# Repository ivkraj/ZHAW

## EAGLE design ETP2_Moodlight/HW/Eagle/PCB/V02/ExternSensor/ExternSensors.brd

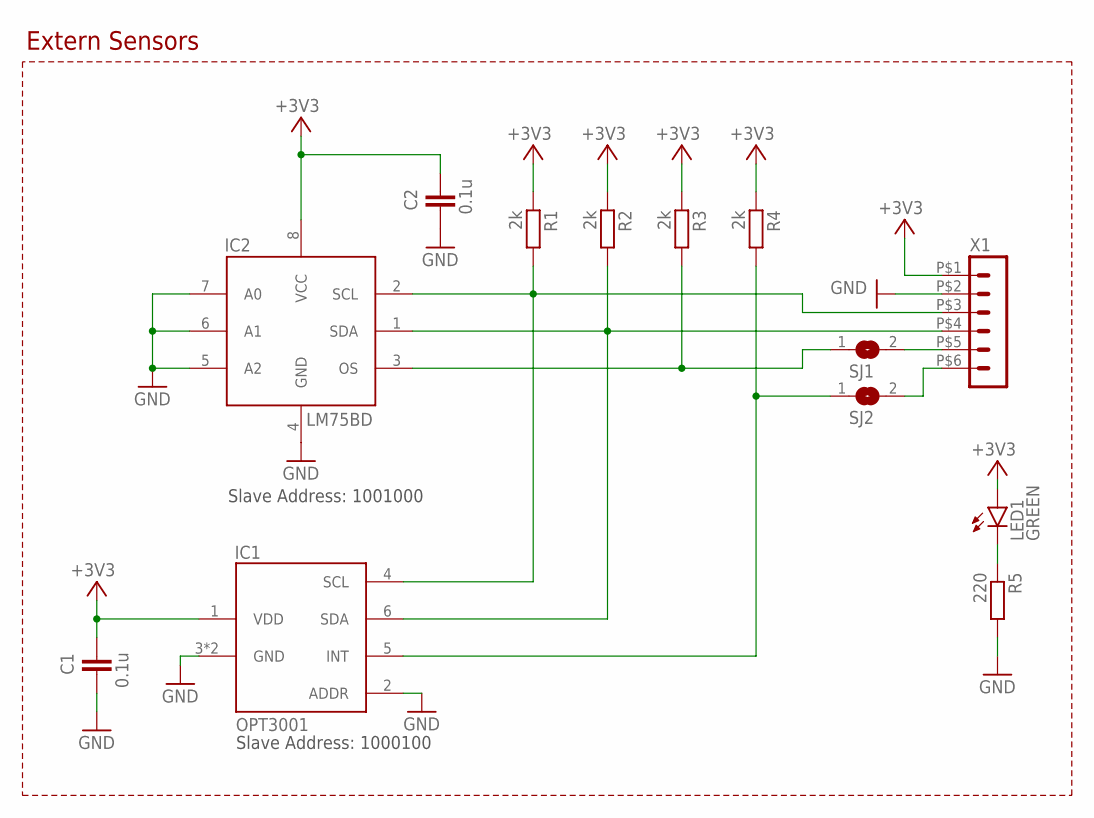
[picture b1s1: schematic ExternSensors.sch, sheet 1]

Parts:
C1, C2: 0.1u; C0805K
IC1: OPT3001
IC2: LM75BD; SO8_LM75
LED1: GREEN; CHIP-LED0805
R1, R2, R3, R4: 2k; R0805
R5: 220; R0805
SJ1, SJ2: SJ
X1: HEADER_POS6_43650-0612; 43650-0612

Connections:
+3V3: C1.2, C2.2, IC1.1 (VDD), IC2.8 (VCC), LED1.A, R1.1, R2.1, R3.1, R4.1, X1.P$1 (1)
GND: C1.1, C2.1, IC1.2 (ADDR), IC1.3 (GND), IC1.P$1 (GND), IC2.4 (GND), IC2.5 (A2), IC2.6 (A1), IC2.7 (A0), R5.2, X1.P$2 (2)
unnamed: LED1.C, R5.1
unnamed: SJ2.2, X1.P$6 (6)
unnamed: IC2.3 (OS), R3.2, SJ1.1
unnamed: IC1.5 (INT), R4.2, SJ2.1
unnamed: SJ1.2, X1.P$5 (5)
SCL: IC1.4 (SCL), IC2.2 (SCL), R1.2, X1.P$3 (3)
SDA: IC1.6 (SDA), IC2.1 (SDA), R2.2, X1.P$4 (4)

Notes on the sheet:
Extern Sensors
Slave Address: 1000100
Slave Address: 1001000

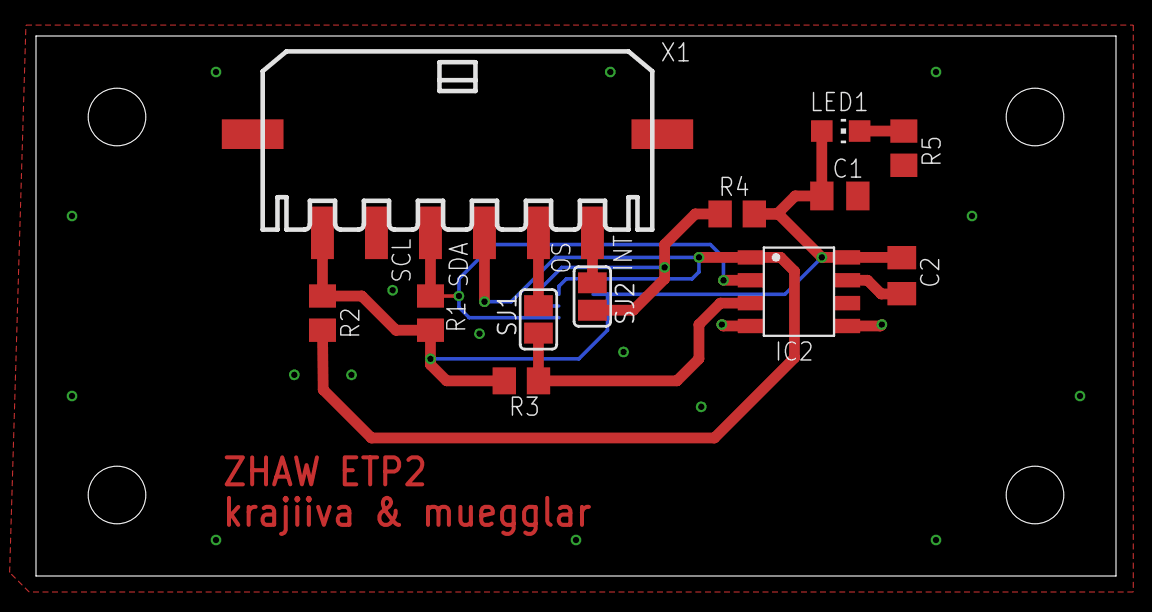
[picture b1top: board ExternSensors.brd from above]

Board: 2 copper layers, 60.0 x 30.0 mm, 13 parts (1 on the bottom side), 9 nets.

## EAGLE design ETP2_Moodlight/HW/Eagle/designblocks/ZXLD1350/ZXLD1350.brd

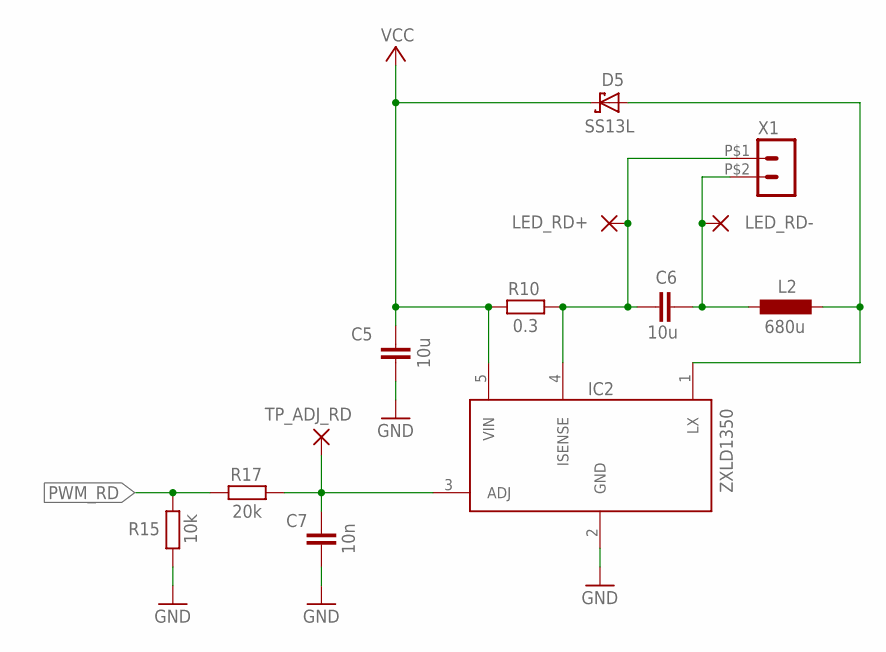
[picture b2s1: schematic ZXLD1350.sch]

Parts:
C5, C6: 10u; C0805K
C7: 10n; C0805K
D5: SS13L; SUB-SMA
IC2: ZXLD1350; TSOT23-5L
L2: 680u; POWER-CHOKE_WE-PD
LED_RD+: TESTPOINT; 3,2/1,6
LED_RD-: TESTPOINT; 3,2/1,6
R10: 0.3; R1206
R15: 10k; R0805
R17: 20k; R0805
TP_ADJ_RD: TESTPOINT; 3,2/1,6
X1: HEADER_POS2_43650-0215; 43650-0215

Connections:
GND: C5.2, C7.2, IC2.2 (GND), R15.1
LED_R+: C6.1, IC2.4 (ISENSE), LED_RD+.1, R10.2, X1.P$1 (1)
LED_R-: C6.2, L2.1, LED_RD-.1, X1.P$2 (2)
unnamed: D5.A, IC2.1 (LX), L2.2
unnamed: C7.1, IC2.3 (ADJ), R17.1, TP_ADJ_RD.1
PWM_RD: R15.2, R17.2
VCC: C5.1, D5.C, IC2.5 (VIN), R10.1

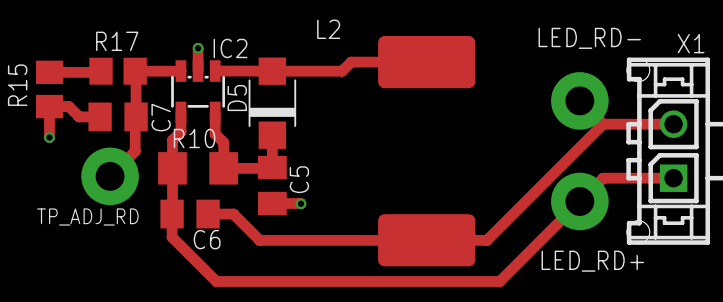
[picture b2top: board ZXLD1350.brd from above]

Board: 2 copper layers, 13 parts (0 on the bottom side), 7 nets.

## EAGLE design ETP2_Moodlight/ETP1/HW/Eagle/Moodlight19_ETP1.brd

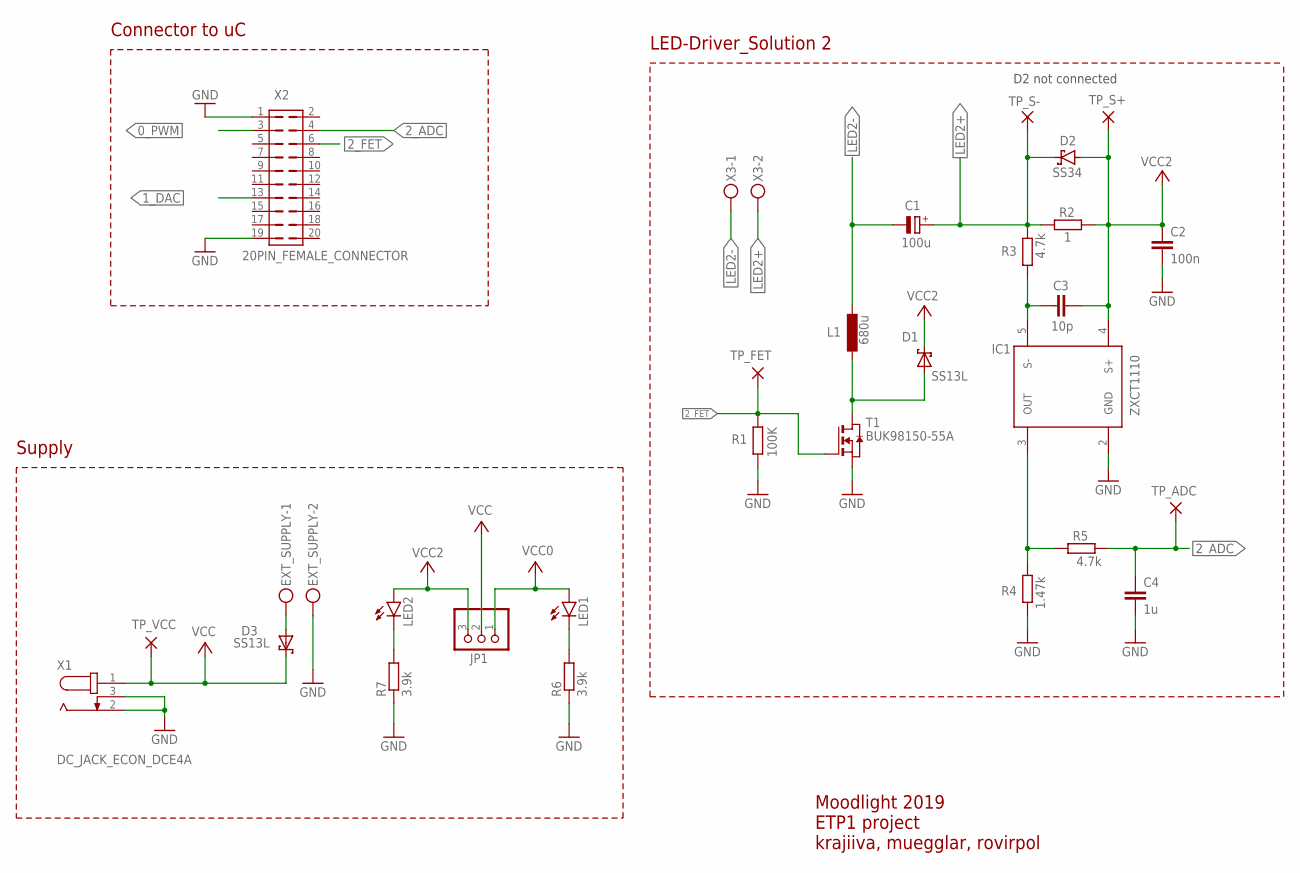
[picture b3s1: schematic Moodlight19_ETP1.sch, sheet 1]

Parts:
C1: 100u; E3,5-8
C2: 100n; C0805K
C3: 10p; C0805K
C4: 1u; C0805K
D1, D3: SS13L; SUB-SMA
D2: SS34; SMC
EXT_SUPPLY: MKDSN1,5/2-5,08
IC1: ZXCT1110; SOT23-5
JP1: PINHD-1X3; 1X03
L1: 680u; POWER-CHOKE_WE-PD
LED1, LED2: LED3MM
R1: 100K; R0805
R2: 1; R1206
R3, R5: 4.7k; R0805
R4: 1.47k; R0805
R6, R7: 3.9k; R0805
T1: BUK98150-55A; SOT223
TP_ADC: WIREPAD4,16O1,6; 4,16O1,6
TP_FET: WIREPAD4,16O1,6; 4,16O1,6
TP_S+: WIREPAD4,16O1,6; 4,16O1,6
TP_S-: WIREPAD4,16O1,6; 4,16O1,6
TP_VCC: WIREPAD4,16O1,6; 4,16O1,6
X1: DC_JACK_ECON_DCE4A
X2: 20PIN_FEMALE_CONNECTOR
X3: MKDSN1,5/2-5,08

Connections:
0_PWM: X2.3; also elsewhere on the board
1_DAC: X2.13; also elsewhere on the board
2_ADC: C4.1, R5.1, TP_ADC.1, X2.4
2_FET: R1.2, T1.1 (G), TP_FET.1, X2.6
A: D3.A, EXT_SUPPLY.1
GND: C2.2, C4.2, EXT_SUPPLY.2, IC1.2 (GND), R1.1, R4.1, R6.1, R7.1, T1.3 (S), X1.2, X1.3, X2.1, X2.19; also elsewhere on the board
LED2+: C1.+, D2.C, R2.1, R3.2, TP_S-.1, X3.2
LED2-: C1.-, L1.1, X3.1
unnamed: LED1.K (C), R6.2
unnamed: LED2.K (C), R7.2
unnamed: IC1.3 (OUT), R4.2, R5.2
unnamed: C3.1, IC1.5 (S-), R3.1
unnamed: D1.A, L1.2, T1.2 (D), T1.4 (D)
VCC: D3.C, JP1.2, TP_VCC.1, X1.1
VCC0: JP1.1, LED1.A; also elsewhere on the board
VCC2: C2.1, C3.2, D1.C, D2.A, IC1.4 (S+), JP1.3, LED2.A, R2.2, TP_S+.1

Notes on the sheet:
Connector to uC
Supply
LED-Driver_Solution 2
Moodlight 2019 ETP1 project krajiiva, muegglar, rovirpol
D2 not connected

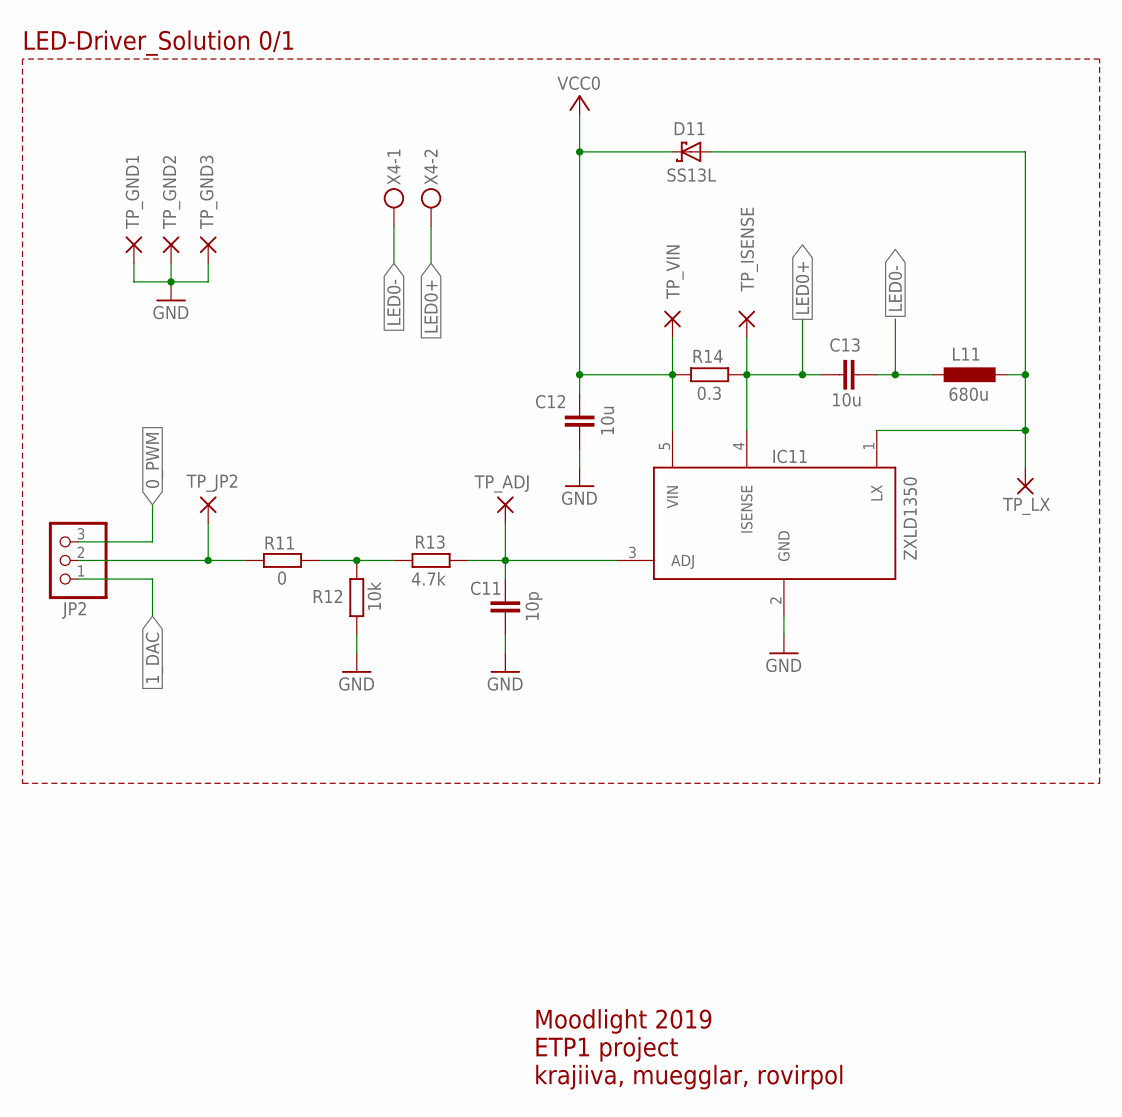
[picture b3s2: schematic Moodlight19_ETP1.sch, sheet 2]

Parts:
C11: 10p; C0805K
C12, C13: 10u; C0805K
D11: SS13L; SUB-SMA
IC11: ZXLD1350; TSOT23-5L
JP2: PINHD-1X3; 1X03
L11: 680u; POWER-CHOKE_WE-PD
R11: 0; R0805
R12: 10k; R0805
R13: 4.7k; R0805
R14: 0.3; R1206
TP_ADJ: WIREPAD4,16O1,6; 4,16O1,6
TP_GND1, TP_GND2, TP_GND3: WIREPAD4,16O1,6; 4,16O1,6
TP_ISENSE: WIREPAD4,16O1,6; 4,16O1,6
TP_JP2: WIREPAD4,16O1,6; 4,16O1,6
TP_LX: WIREPAD4,16O1,6; 4,16O1,6
TP_VIN: WIREPAD4,16O1,6; 4,16O1,6
X4: MKDSN1,5/2-5,08

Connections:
0_ADJUST: JP2.2, R11.1, TP_JP2.1
0_PWM: JP2.3; also elsewhere on the board
1_DAC: JP2.1; also elsewhere on the board
GND: C11.2, C12.2, IC11.2 (GND), R12.1, TP_GND1.1, TP_GND2.1, TP_GND3.1; also elsewhere on the board
LED0+: C13.1, IC11.4 (ISENSE), R14.2, TP_ISENSE.1, X4.2
LED0-: C13.2, L11.1, X4.1
unnamed: R11.2, R12.2, R13.2
unnamed: D11.A, IC11.1 (LX), L11.2, TP_LX.1
unnamed: C11.1, IC11.3 (ADJ), R13.1, TP_ADJ.1
VCC0: C12.1, D11.C, IC11.5 (VIN), R14.1, TP_VIN.1; also elsewhere on the board

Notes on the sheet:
LED-Driver_Solution 0/1
Moodlight 2019 ETP1 project krajiiva, muegglar, rovirpol

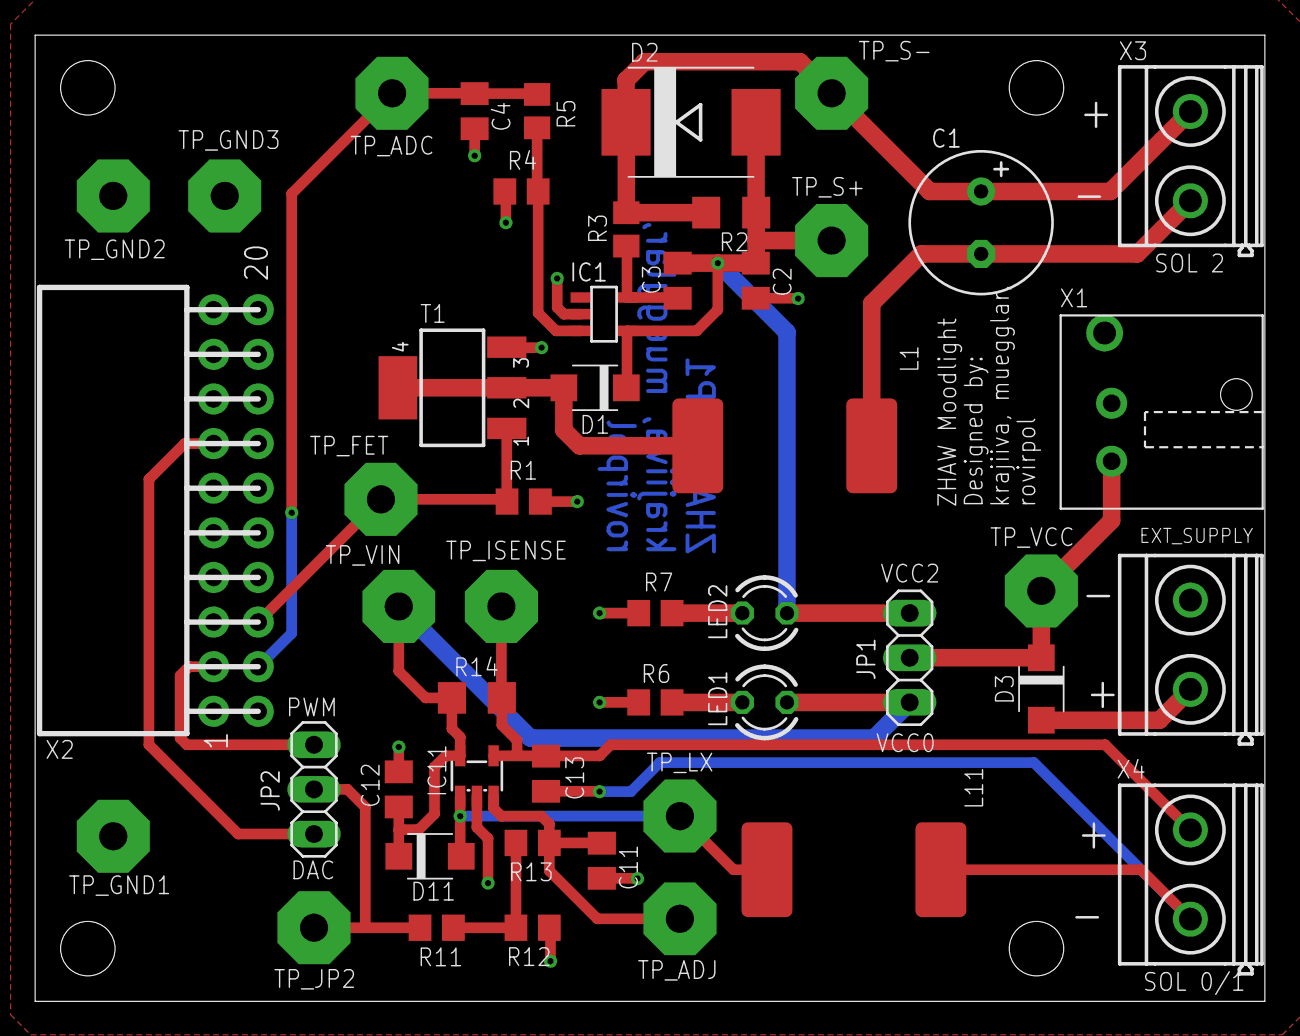
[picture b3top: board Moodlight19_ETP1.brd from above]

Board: 2 copper layers, 70.0 x 55.0 mm, 49 parts (0 on the bottom side), 22 nets.

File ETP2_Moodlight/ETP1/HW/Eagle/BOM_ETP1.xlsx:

Part | Value | Device | Package | Description
C1 | 100u | CPOL-EUE3.5-8 | E3,5-8 | POLARIZED CAPACITOR, European symbol
C2 | 100n | C-EUC0805K | C0805K | CAPACITOR, European symbol
C3 | 10p | C-EUC0805K | C0805K | CAPACITOR, European symbol
C4 | 1u | C-EUC0805K | C0805K | CAPACITOR, European symbol
C11 | 10p | C-EUC0805K | C0805K | CAPACITOR, European symbol
C12 | 10u | C-EUC0805K | C0805K | CAPACITOR, European symbol
C13 | 10u | C-EUC0805K | C0805K | CAPACITOR, European symbol
D1 | SS13L | SS13L | SUB-SMA | Schottky-Diode
D2 | SS34 | SCHOTTKY-DIODESMC | SMC | Schottky Diode
D3 | SS13L | SS13L | SUB-SMA | Schottky-Diode
D11 | SS13L | SS13L | SUB-SMA | Schottky-Diode
EXT_SUPPLY | MKDSN1,5/2-5,08 | MKDSN1,5/2-5,08 | MKDSN1,5/2-5,08 | MKDSN 1,5/ 2-5,08 Printklemme
IC1 | ZXCT1110 | ZXCT1110 | SOT23-5 | ZXCT1110
IC11 | ZXLD1350 | ZXLD1350 | TSOT23-5L | ZXLD1350
JP1 |  | PINHD-1X3 | 1X03 | PIN HEADER
JP2 |  | PINHD-1X3 | 1X03 | PIN HEADER
L1 | 680u | POWER-CHOKE_WE-PD | POWER-CHOKE_WE-PD | POWER-CHOKE_WE-PD
L11 | 680u | POWER-CHOKE_WE-PD | POWER-CHOKE_WE-PD | POWER-CHOKE_WE-PD
LED1 |  | LED3MM | LED3MM | LED
LED2 |  | LED3MM | LED3MM | LED
R1 | 100K | R-EU_R0805 | R0805 | RESISTOR, European symbol
R2 | 1 | R-EU_R1206 | R1206 | RESISTOR, European symbol
R3 | 4.7k | R-EU_R0805 | R0805 | RESISTOR, European symbol
R4 | 1.47k | R-EU_R0805 | R0805 | RESISTOR, European symbol
R5 | 4.7k | R-EU_R0805 | R0805 | RESISTOR, European symbol
R6 | 1.2k | R-EU_R0805 | R0805 | RESISTOR, European symbol
R7 | 1.2k | R-EU_R0805 | R0805 | RESISTOR, European symbol
R11 | 2k | R-EU_R0805 | R0805 | RESISTOR, European symbol
R12 | 1.3k | R-EU_R0805 | R0805 | RESISTOR, European symbol
R13 | 4.7k | R-EU_R0805 | R0805 | RESISTOR, European symbol
R14 | 0.3 | R-EU_R1206 | R1206 | RESISTOR, European symbol
T1 | BUK98150-55A | BUK98150-55A | SOT223 | n-Kanal-MOS-FET
TP_ADC | WIREPAD4,16O1,6 | WIREPAD4,16O1,6 | 4,16O1,6 | Wire PAD connect wire on PCB
TP_ADJ | WIREPAD4,16O1,6 | WIREPAD4,16O1,6 | 4,16O1,6 | Wire PAD connect wire on PCB
TP_FET | WIREPAD4,16O1,6 | WIREPAD4,16O1,6 | 4,16O1,6 | Wire PAD connect wire on PCB
TP_GND1 | WIREPAD4,16O1,6 | WIREPAD4,16O1,6 | 4,16O1,6 | Wire PAD connect wire on PCB
TP_GND2 | WIREPAD4,16O1,6 | WIREPAD4,16O1,6 | 4,16O1,6 | Wire PAD connect wire on PCB
TP_GND3 | WIREPAD4,16O1,6 | WIREPAD4,16O1,6 | 4,16O1,6 | Wire PAD connect wire on PCB
TP_ISENSE | WIREPAD4,16O1,6 | WIREPAD4,16O1,6 | 4,16O1,6 | Wire PAD connect wire on PCB
TP_JP2 | WIREPAD4,16O1,6 | WIREPAD4,16O1,6 | 4,16O1,6 | Wire PAD connect wire on PCB
TP_LX | WIREPAD4,16O1,6 | WIREPAD4,16O1,6 | 4,16O1,6 | Wire PAD connect wire on PCB
TP_S+ | WIREPAD4,16O1,6 | WIREPAD4,16O1,6 | 4,16O1,6 | Wire PAD connect wire on PCB
TP_S- | WIREPAD4,16O1,6 | WIREPAD4,16O1,6 | 4,16O1,6 | Wire PAD connect wire on PCB
TP_VCC | WIREPAD4,16O1,6 | WIREPAD4,16O1,6 | 4,16O1,6 | Wire PAD connect wire on PCB
TP_VIN | WIREPAD4,16O1,6 | WIREPAD4,16O1,6 | 4,16O1,6 | Wire PAD connect wire on PCB
X1 | DC_JACK_ECON_DCE4A | DC_JACK_ECON_DCE4A | DC_JACK_ECON_DCE4A | DC_JACK_ECON_DCE4A
X2 | 20PIN_FEMALE_CONNECTOR | 20PIN_FEMALE_CONNECTOR | 20PIN_FEMALE_CONNECTOR | Buchsenleiste 20Pol 90Â°
X3 | MKDSN1,5/2-5,08 | MKDSN1,5/2-5,08 | MKDSN1,5/2-5,08 | MKDSN 1,5/ 2-5,08 Printklemme
X4 | MKDSN1,5/2-5,08 | MKDSN1,5/2-5,08 | MKDSN1,5/2-5,08 | MKDSN 1,5/ 2-5,08 Printklemme

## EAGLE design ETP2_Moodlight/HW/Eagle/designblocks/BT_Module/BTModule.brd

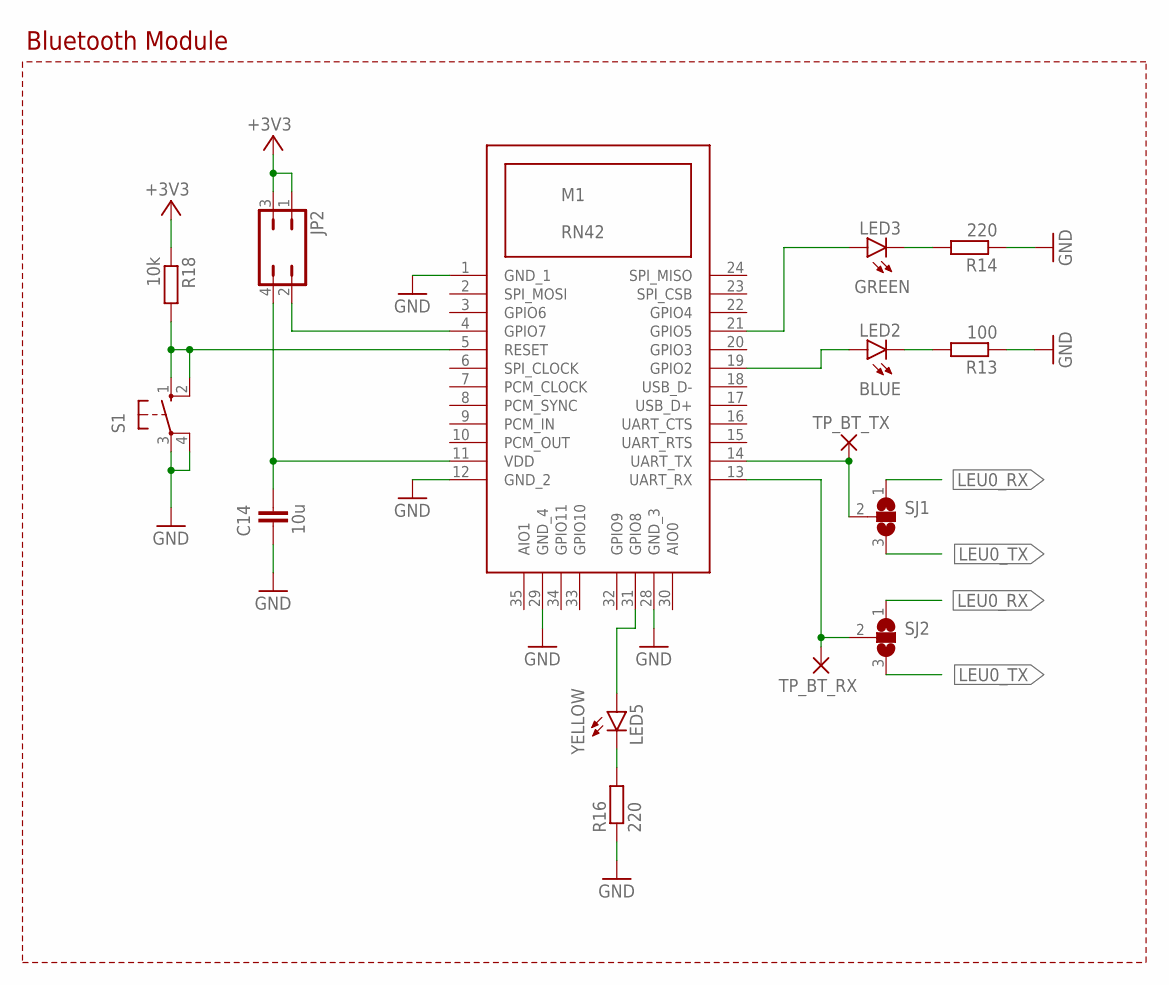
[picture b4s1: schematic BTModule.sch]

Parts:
C14: 10u; C0805K
JP2: JP2Q
LED2: BLUE; CHIP-LED0805
LED3: GREEN; CHIP-LED0805
LED5: YELLOW; CHIP-LED0805
M1: RN42_BLUETOOTH
R13: 100; R0805
R14, R16: 220; R0805
R18: 10k; R0805
S1: 10-XX; B3F-10XX
SJ1, SJ2: SJ2W; SJ_2
TP_BT_RX: TESTPOINT; 3,2/1,6
TP_BT_TX: TESTPOINT; 3,2/1,6

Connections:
+3V3: JP2.1, JP2.3, R18.1
GND: C14.1, M1.1 (GND_1), M1.12 (GND_2), M1.28 (GND_3), M1.29 (GND_4), R13.1, R14.1, R16.1, S1.3, S1.4 (P1)
LEU0_RX: SJ1.1, SJ2.1
LEU0_TX: SJ1.3, SJ2.3
unnamed: JP2.2, M1.4 (GPIO7)
unnamed: C14.2, JP2.4, M1.11 (VDD)
unnamed: LED2.C, R13.2
unnamed: LED2.A, M1.19 (GPIO2)
unnamed: LED3.C, R14.2
unnamed: LED3.A, M1.21 (GPIO5)
unnamed: LED5.C, R16.2
unnamed: LED5.A, M1.31 (GPIO8)
unnamed: M1.5 (RESET), R18.2, S1.1 (S), S1.2 (S1)
unnamed: M1.14 (UART_TX), SJ1.2, TP_BT_TX.1
unnamed: M1.13 (UART_RX), SJ2.2, TP_BT_RX.1

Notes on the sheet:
Bluetooth Module

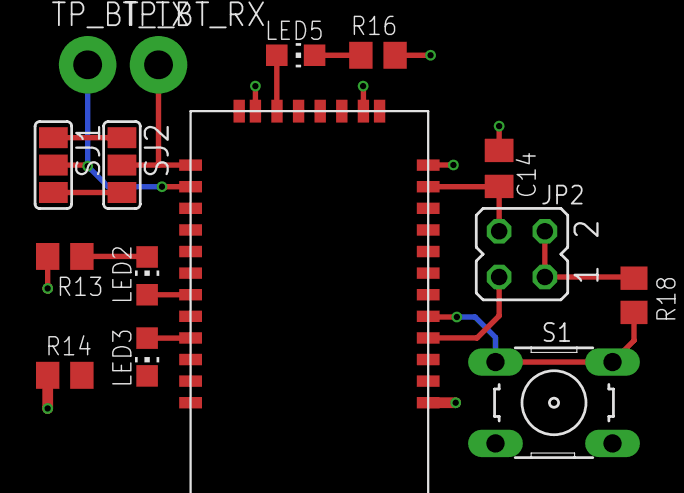
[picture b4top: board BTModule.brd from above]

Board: 2 copper layers, 15 parts (0 on the bottom side), 15 nets.

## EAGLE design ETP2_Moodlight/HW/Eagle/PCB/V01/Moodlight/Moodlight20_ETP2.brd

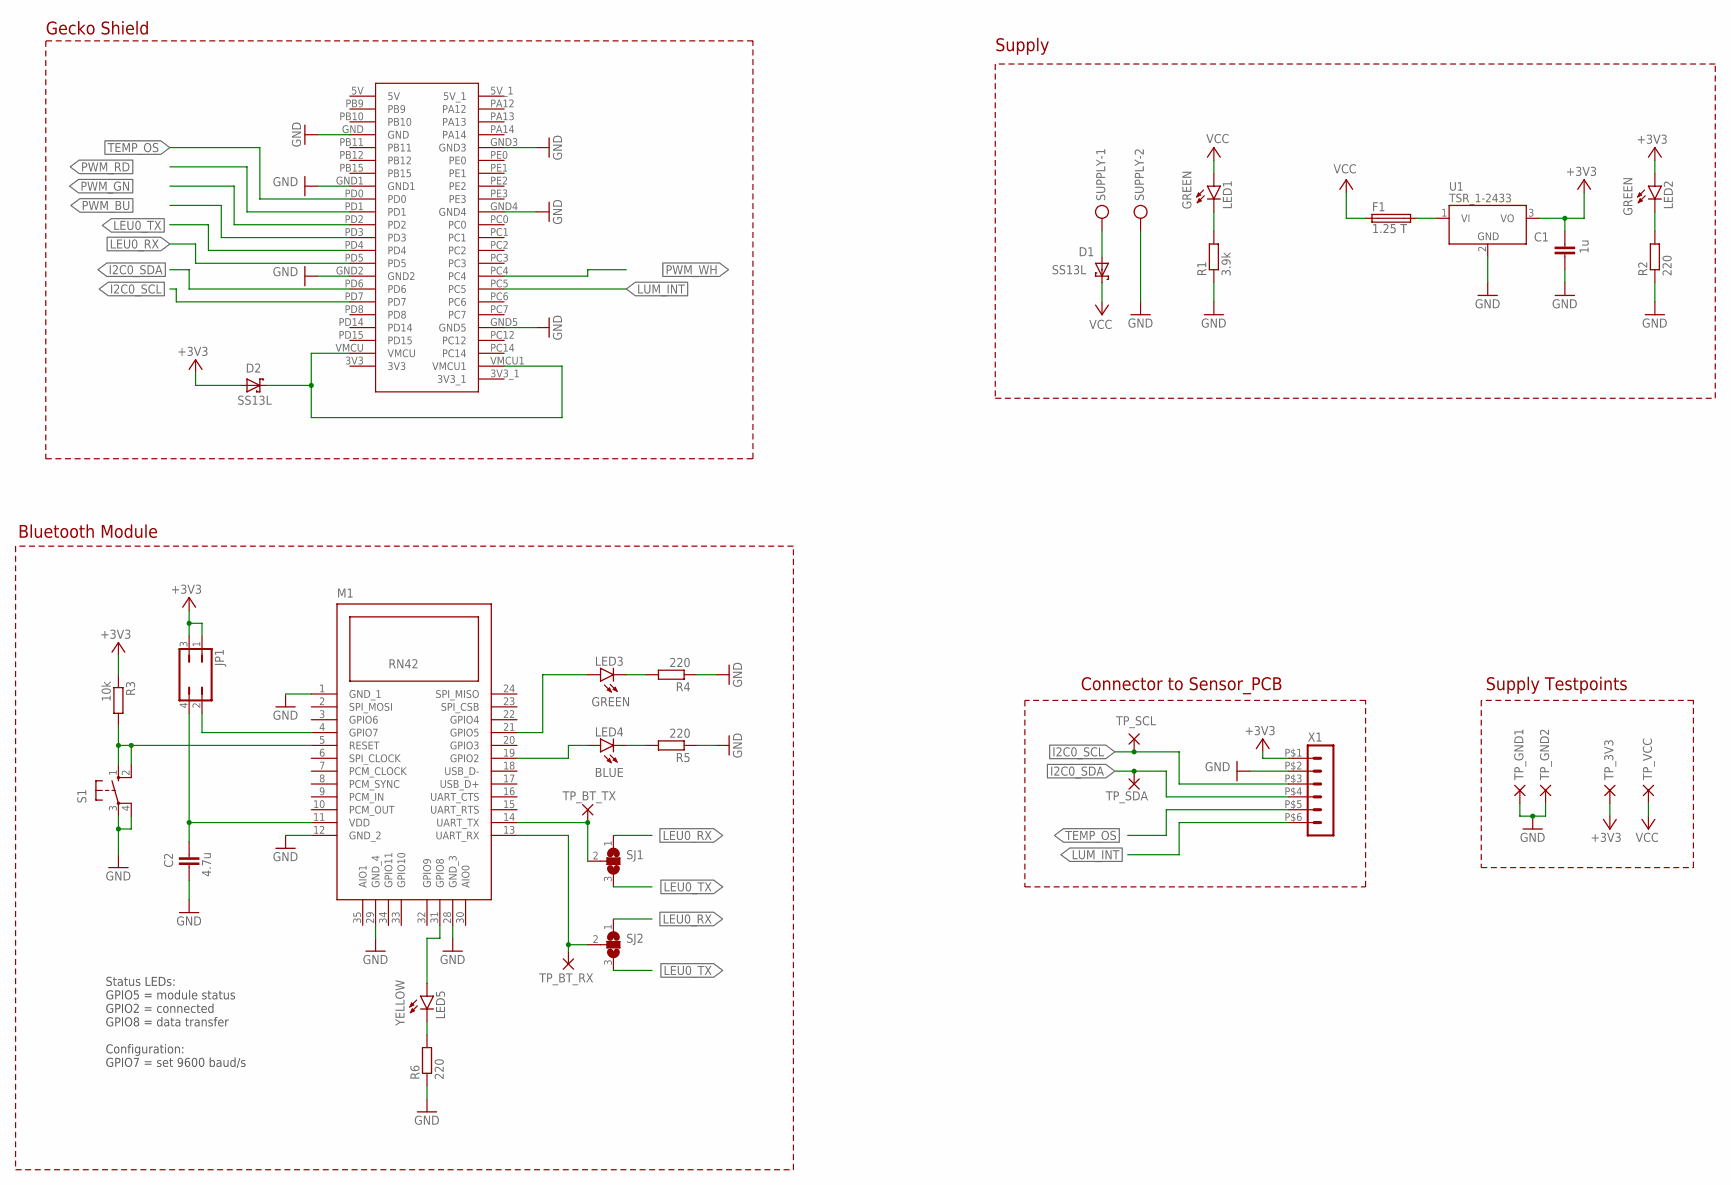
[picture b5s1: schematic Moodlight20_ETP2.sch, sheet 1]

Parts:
C1: 1u; C0805K
C2: 4.7u; C0805K
D1, D2: SS13L; SUB-SMA
F1: 1.25 T; 19560
GECKO: GECKO_SHIELD
JP1: JP2Q
LED1, LED2, LED3: GREEN; CHIP-LED0805
LED4: BLUE; CHIP-LED0805
LED5: YELLOW; CHIP-LED0805
M1: RN42_BLUETOOTH
R1: 3.9k; R0805
R2, R4, R5, R6: 220; R0805
R3: 10k; R0805
S1: 10-XX; B3F-10XX
SJ1, SJ2: SJ2W; SJ_2
SUPPLY: MKDSN1,5/2-5,08
TP_3V3: TESTPOINT; 3,2/1,6
TP_BT_RX: TESTPOINT; 3,2/1,6
TP_BT_TX: TESTPOINT; 3,2/1,6
TP_GND1, TP_GND2: TESTPOINT; 3,2/1,6
TP_SCL: TESTPOINT; 3,2/1,6
TP_SDA: TESTPOINT; 3,2/1,6
TP_VCC: TESTPOINT; 3,2/1,6
U1: TSR_1-2433; TSR-1
X1: HEADER_POS6_43045-0612; 43045-0612

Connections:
+3V3: C1.1, D2.A, JP1.1, JP1.3, LED2.A, R3.1, TP_3V3.1, U1.3 (VO), X1.P$1 (1)
A1: D1.A, SUPPLY.1
GND: C1.2, C2.1, GECKO.GND, GECKO.GND1, GECKO.GND2, GECKO.GND3, GECKO.GND4, GECKO.GND5, M1.1 (GND_1), M1.12 (GND_2), M1.28 (GND_3), M1.29 (GND_4), R1.1, R2.1, R4.1, R5.1, R6.1, S1.3, S1.4 (P1), SUPPLY.2, TP_GND1.1, TP_GND2.1, U1.2 (GND), X1.P$2 (2); also elsewhere on the board
I2C0_SCL: GECKO.PD7, TP_SCL.1, X1.P$3 (3)
I2C0_SDA: GECKO.PD6, TP_SDA.1, X1.P$4 (4)
LEU0_RX: GECKO.PD5, SJ1.1, SJ2.1
LEU0_TX: GECKO.PD4, SJ1.3, SJ2.3
LUM_INT: GECKO.PC5, X1.P$6 (6)
unnamed: LED2.C, R2.2
unnamed: D2.C, GECKO.VMCU, GECKO.VMCU1
unnamed: LED1.C, R1.2
unnamed: JP1.2, M1.4 (GPIO7)
unnamed: C2.2, JP1.4, M1.11 (VDD)
unnamed: LED4.C, R5.2
unnamed: LED4.A, M1.19 (GPIO2)
unnamed: LED3.C, R4.2
unnamed: LED3.A, M1.21 (GPIO5)
unnamed: LED5.C, R6.2
unnamed: LED5.A, M1.31 (GPIO8)
unnamed: M1.5 (RESET), R3.2, S1.1 (S), S1.2 (S1)
unnamed: M1.14 (UART_TX), SJ1.2, TP_BT_TX.1
unnamed: M1.13 (UART_RX), SJ2.2, TP_BT_RX.1
PWM_BU: GECKO.PD3; also elsewhere on the board
PWM_GN: GECKO.PD2; also elsewhere on the board
PWM_RD: GECKO.PD1; also elsewhere on the board
PWM_WH: GECKO.PC4; also elsewhere on the board
TEMP_OS: GECKO.PD0, X1.P$5 (5)
VCC: D1.C, F1.1, LED1.A, TP_VCC.1; also elsewhere on the board
VI: F1.2, U1.1 (VI)

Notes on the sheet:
Supply
Supply Testpoints
Connector to Sensor_PCB
Bluetooth Module
Gecko Shield
Status LEDs: GPIO5 = module status GPIO2 = connected GPIO8 = data transfer Configuration: GPIO7 = set 9600 baud/s

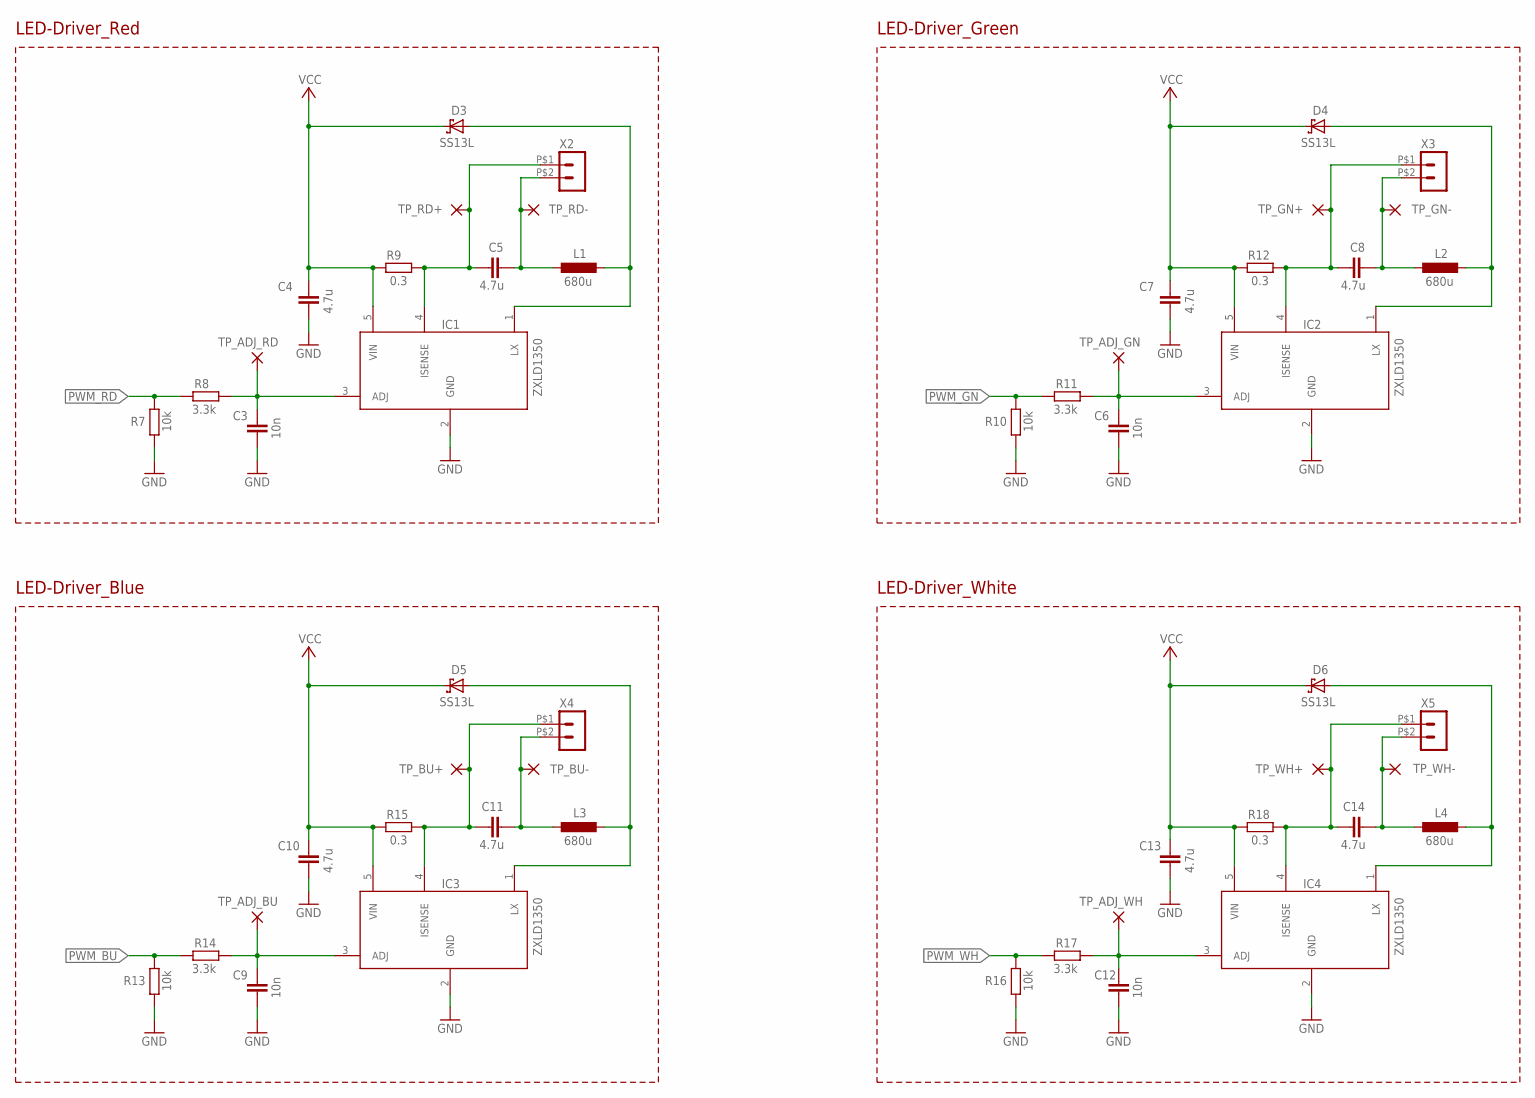
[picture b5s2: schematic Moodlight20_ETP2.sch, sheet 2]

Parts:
C3, C6, C9, C12: 10n; C0805K
C4, C5, C7, C8, C10, C11, C13, C14: 4.7u; C0805K
D3, D4, D5, D6: SS13L; SUB-SMA
IC1, IC2, IC3, IC4: ZXLD1350; TSOT23-5L
L1, L2, L3, L4: 680u; POWER-CHOKE_WE-PD
R7, R10, R13, R16: 10k; R0805
R8, R11, R14, R17: 3.3k; R0805
R9, R12, R15, R18: 0.3; R1206
TP_ADJ_BU: TESTPOINT; 3,2/1,6
TP_ADJ_GN: TESTPOINT; 3,2/1,6
TP_ADJ_RD: TESTPOINT; 3,2/1,6
TP_ADJ_WH: TESTPOINT; 3,2/1,6
TP_BU+: TESTPOINT; 3,2/1,6
TP_BU-: TESTPOINT; 3,2/1,6
TP_GN+: TESTPOINT; 3,2/1,6
TP_GN-: TESTPOINT; 3,2/1,6
TP_RD+: TESTPOINT; 3,2/1,6
TP_RD-: TESTPOINT; 3,2/1,6
TP_WH+: TESTPOINT; 3,2/1,6
TP_WH-: TESTPOINT; 3,2/1,6
X2, X3, X4, X5: HEADER_POS2_43650-0215; 43650-0215

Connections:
GND: C3.2, C4.2, C6.2, C7.2, C9.2, C10.2, C12.2, C13.2, IC1.2 (GND), IC2.2 (GND), IC3.2 (GND), IC4.2 (GND), R7.1, R10.1, R13.1, R16.1; also elsewhere on the board
LED_R+1: C5.1, IC1.4 (ISENSE), R9.2, TP_RD+.1, X2.P$1 (1)
LED_R+2: C14.1, IC4.4 (ISENSE), R18.2, TP_WH+.1, X5.P$1 (1)
LED_R+3: C8.1, IC2.4 (ISENSE), R12.2, TP_GN+.1, X3.P$1 (1)
LED_R+5: C11.1, IC3.4 (ISENSE), R15.2, TP_BU+.1, X4.P$1 (1)
LED_R-1: C5.2, L1.1, TP_RD-.1, X2.P$2 (2)
LED_R-2: C14.2, L4.1, TP_WH-.1, X5.P$2 (2)
LED_R-3: C8.2, L2.1, TP_GN-.1, X3.P$2 (2)
LED_R-5: C11.2, L3.1, TP_BU-.1, X4.P$2 (2)
unnamed: D3.A, IC1.1 (LX), L1.2
unnamed: C3.1, IC1.3 (ADJ), R8.1, TP_ADJ_RD.1
unnamed: D6.A, IC4.1 (LX), L4.2
unnamed: C12.1, IC4.3 (ADJ), R17.1, TP_ADJ_WH.1
unnamed: D4.A, IC2.1 (LX), L2.2
unnamed: C6.1, IC2.3 (ADJ), R11.1, TP_ADJ_GN.1
unnamed: D5.A, IC3.1 (LX), L3.2
unnamed: C9.1, IC3.3 (ADJ), R14.1, TP_ADJ_BU.1
PWM_BU: R13.2, R14.2; also elsewhere on the board
PWM_GN: R10.2, R11.2; also elsewhere on the board
PWM_RD: R7.2, R8.2; also elsewhere on the board
PWM_WH: R16.2, R17.2; also elsewhere on the board
VCC: C4.1, C7.1, C10.1, C13.1, D3.C, D4.C, D5.C, D6.C, IC1.5 (VIN), IC2.5 (VIN), IC3.5 (VIN), IC4.5 (VIN), R9.1, R12.1, R15.1, R18.1; also elsewhere on the board

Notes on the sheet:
LED-Driver_Red
LED-Driver_Green
LED-Driver_Blue
LED-Driver_White

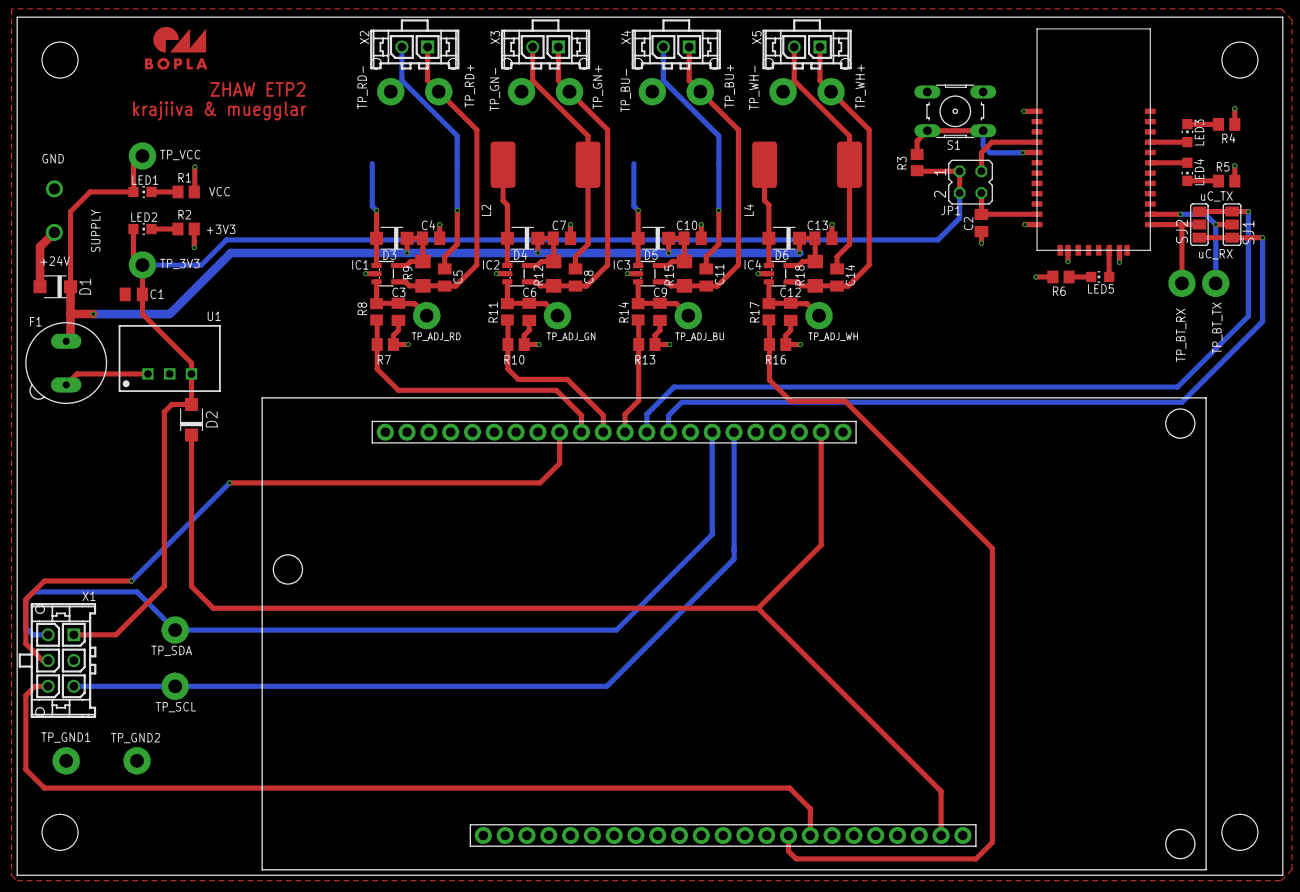
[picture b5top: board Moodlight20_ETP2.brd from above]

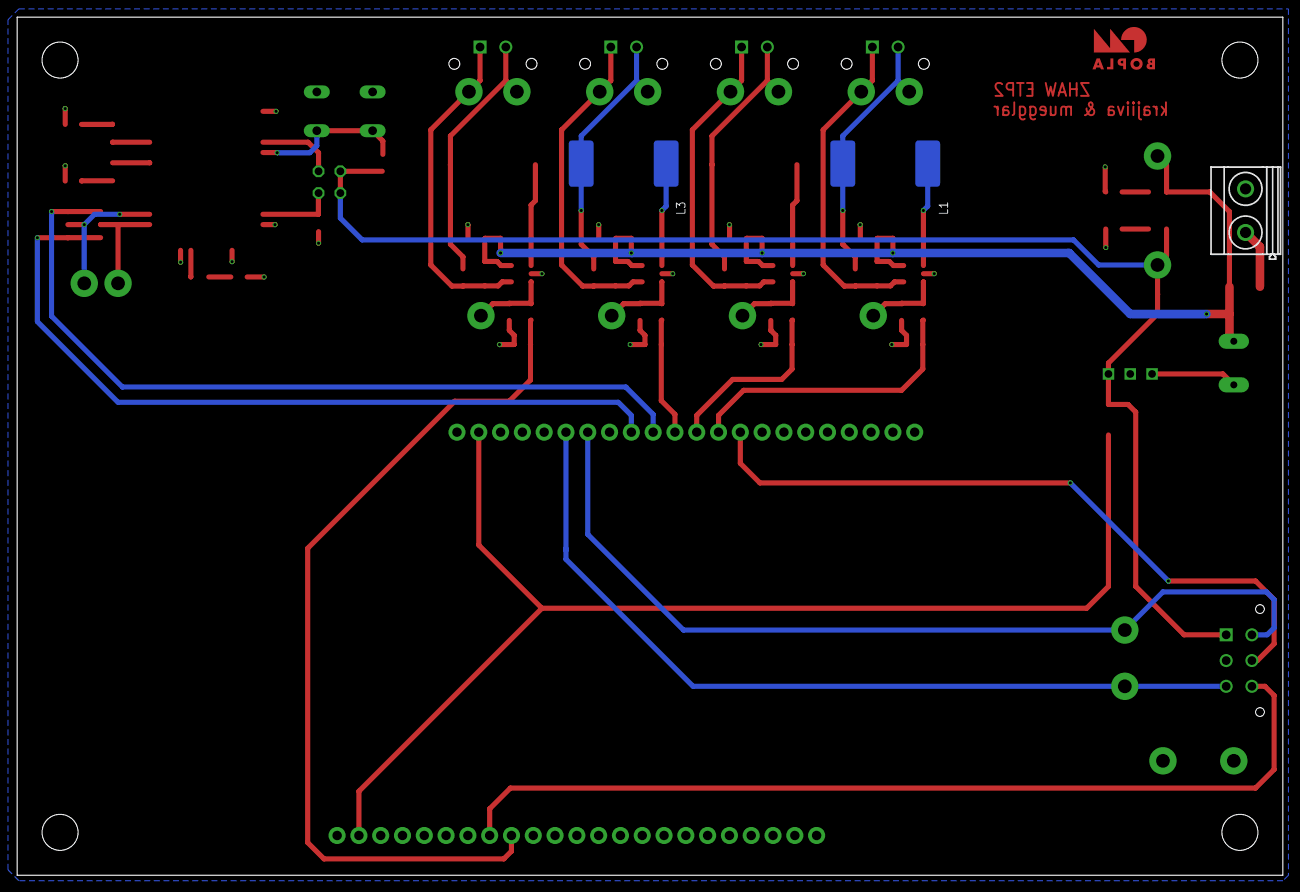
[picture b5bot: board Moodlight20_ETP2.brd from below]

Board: 2 copper layers, 147.5 x 100.0 mm, 85 parts (3 on the bottom side), 45 nets.

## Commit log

2021-09-19 Rotz
2021-09-19 Chum loos
2021-09-21 Add files via upload
    Initial Commit
2021-09-21 loos
2021-09-21 bitte goh eifach
